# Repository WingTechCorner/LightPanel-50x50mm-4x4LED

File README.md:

# LightPanel 50x50mm 4x6 LED

A 4x6 grid of white LED on a 50x50mm panel with M3 mounting holes inset 4mm from the corners.

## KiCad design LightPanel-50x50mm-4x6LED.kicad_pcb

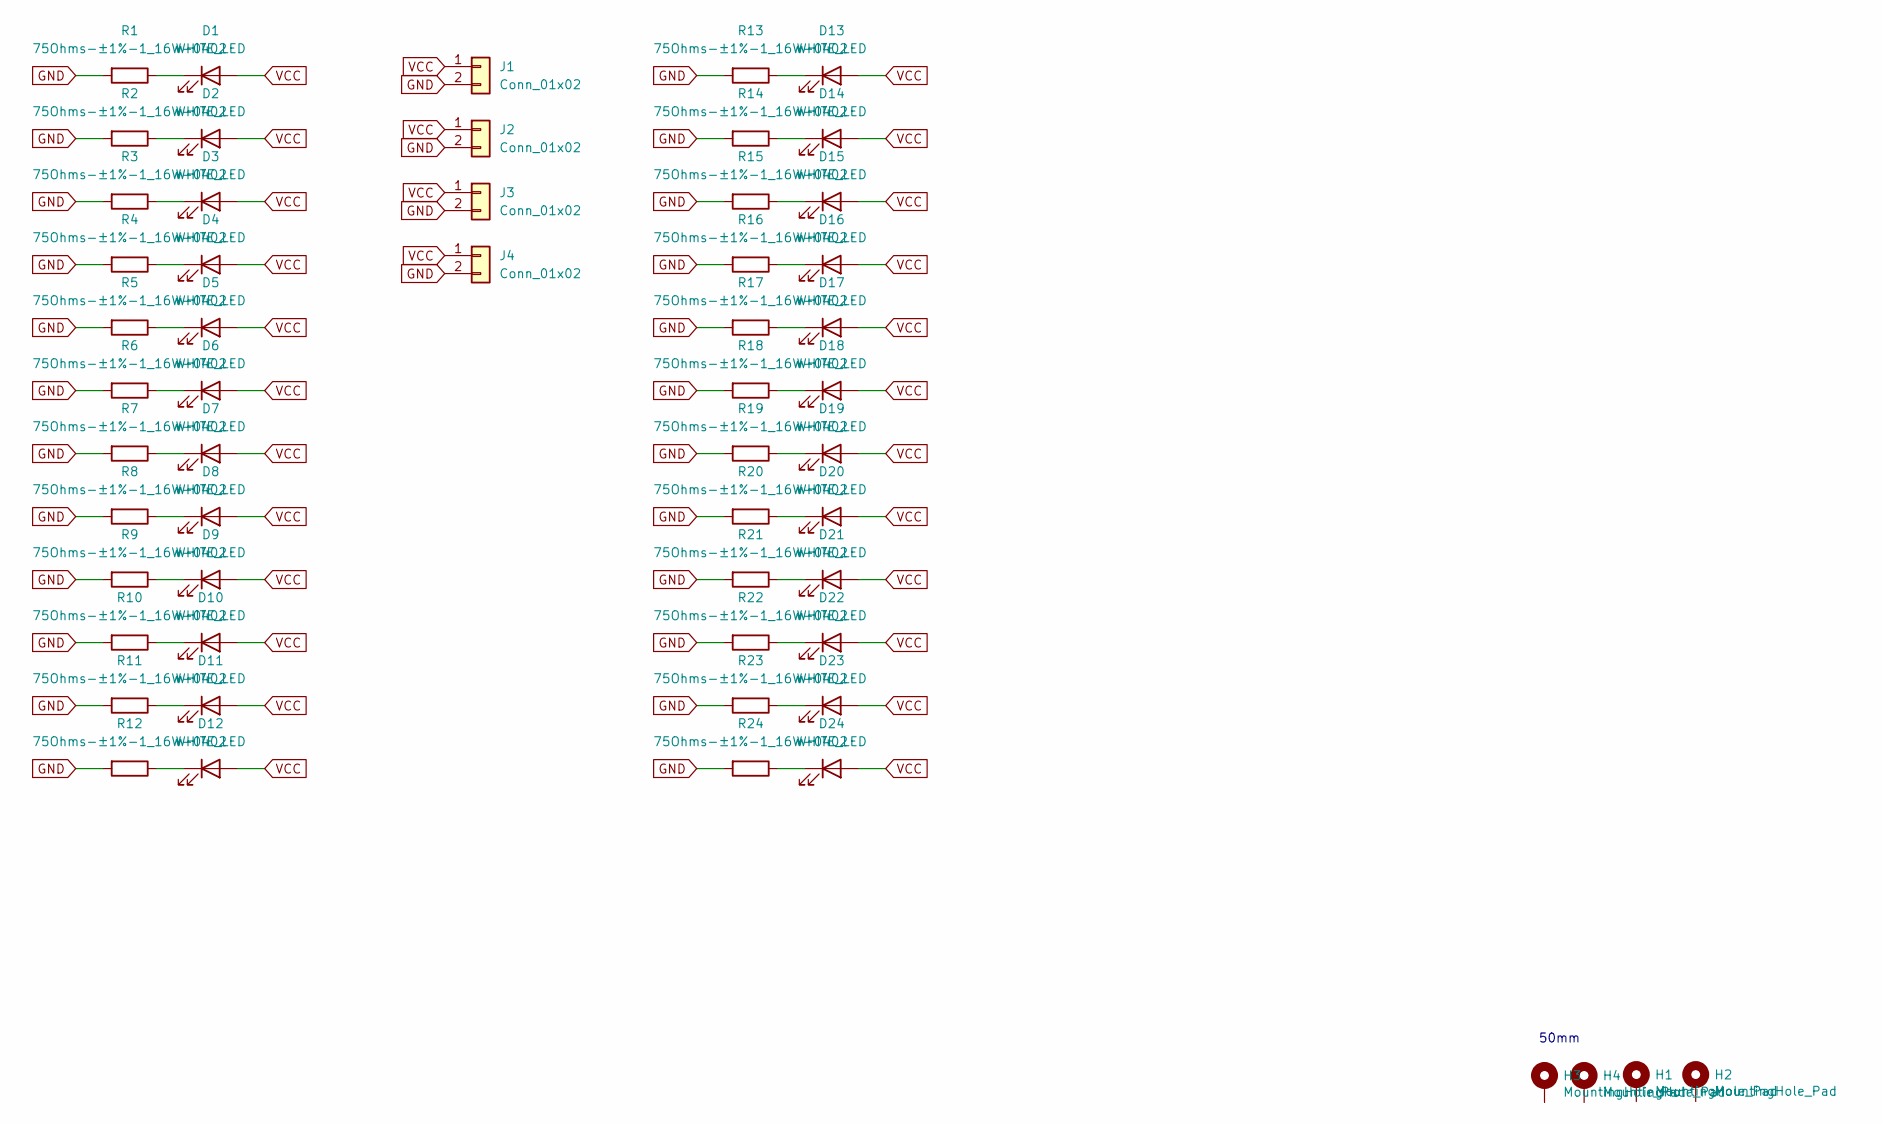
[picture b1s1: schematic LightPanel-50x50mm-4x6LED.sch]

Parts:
D1, D2, D3, D4, D5, D6, D7, D8, D9, D10, D11, D12, D13, D14, D15, D16, D17, D18, D19, D20, D21, D22, D23, D24: WHITE_LED; D_0603_1608Metric; JLCPCBPART C2290
H1, H2, H3, H4: MountingHole_Pad; MountingHole_3.2mm_M3_Pad_Via
J1, J2, J3, J4: Conn_01x02; PinHeader_1x02_P2.54mm_Vertical
R1, R2, R3, R4, R5, R6, R7, R8, R9, R10, R11, R12, R13, R14, R15, R16, R17, R18, R19, R20, R21, R22, R23, R24: 75Ohms-±1%-1_16W-0402; R_0402_1005Metric; JLCPCB C25133

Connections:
GND: J1.2, J2.2, J3.2, J4.2, R1.2, R2.2, R3.2, R4.2, R5.2, R6.2, R7.2, R8.2, R9.2, R10.2, R11.2, R12.2, R13.2, R14.2, R15.2, R16.2, R17.2, R18.2, R19.2, R20.2, R21.2, R22.2, R23.2, R24.2
unnamed: D1.1 (K), R1.1
unnamed: D2.1 (K), R2.1
unnamed: D3.1 (K), R3.1
unnamed: D4.1 (K), R4.1
unnamed: D5.1 (K), R5.1
unnamed: D6.1 (K), R6.1
unnamed: D7.1 (K), R7.1
unnamed: D8.1 (K), R8.1
unnamed: D9.1 (K), R9.1
unnamed: D10.1 (K), R10.1
unnamed: D11.1 (K), R11.1
unnamed: D12.1 (K), R12.1
unnamed: D13.1 (K), R13.1
unnamed: D14.1 (K), R14.1
unnamed: D15.1 (K), R15.1
unnamed: D16.1 (K), R16.1
unnamed: D17.1 (K), R17.1
unnamed: D18.1 (K), R18.1
unnamed: D19.1 (K), R19.1
unnamed: D20.1 (K), R20.1
unnamed: D21.1 (K), R21.1
unnamed: D22.1 (K), R22.1
unnamed: D23.1 (K), R23.1
unnamed: D24.1 (K), R24.1
VCC: D1.2 (A), D2.2 (A), D3.2 (A), D4.2 (A), D5.2 (A), D6.2 (A), D7.2 (A), D8.2 (A), D9.2 (A), D10.2 (A), D11.2 (A), D12.2 (A), D13.2 (A), D14.2 (A), D15.2 (A), D16.2 (A), D17.2 (A), D18.2 (A), D19.2 (A), D20.2 (A), D21.2 (A), D22.2 (A), D23.2 (A), D24.2 (A), J1.1, J2.1, J3.1, J4.1

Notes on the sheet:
50mm

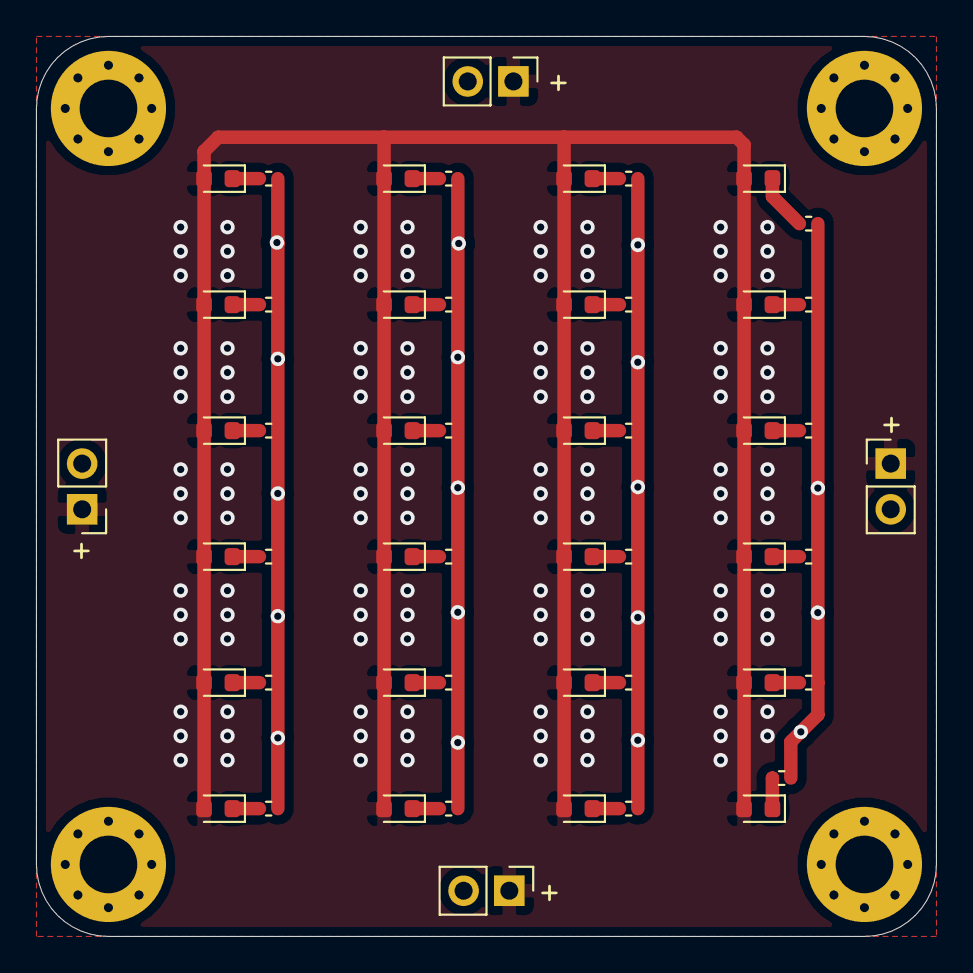
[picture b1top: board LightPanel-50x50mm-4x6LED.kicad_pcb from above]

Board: 2 copper layers, 50.0 x 50.0 mm, 56 parts (0 on the bottom side), 26 nets.

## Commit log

2021-05-15 Kicad files initial add
2021-05-15 Update with images
